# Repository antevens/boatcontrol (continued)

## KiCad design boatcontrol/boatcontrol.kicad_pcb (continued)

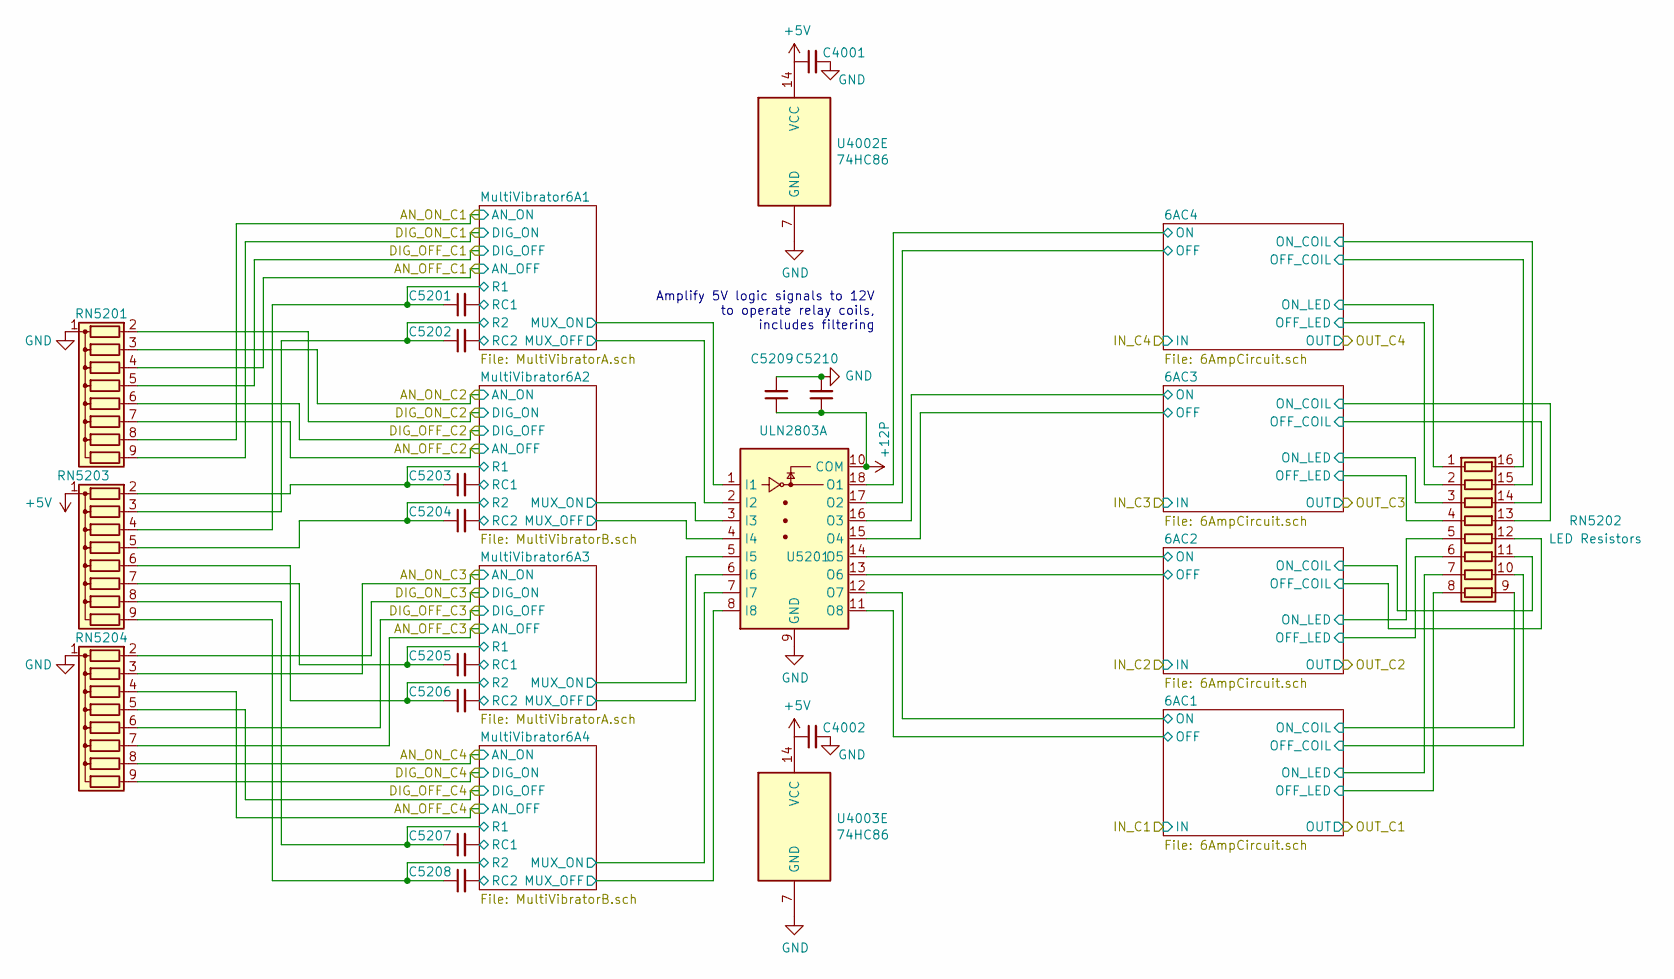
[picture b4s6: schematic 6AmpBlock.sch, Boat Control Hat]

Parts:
C4001, C4002, C7910: 0.1uF; C_Disc_D7.5mm_W5.0mm_P5.00mm
C5201, C5202, C5203, C5204, C5205, C5206, C5207, C5208: 1µF; C_Disc_D7.5mm_W5.0mm_P5.00mm
C7909: 10uF; C_Disc_D7.5mm_W5.0mm_P5.00mm
RN7901, RN7904: 100KΩ; R_Array_SIP9; Manufacturer_Part_Number 4609X-101-105LF
RN7902: 680Ω; DIP254P762X432-16P
RN7903: 10MΩ; R_Array_SIP9
U7901: ULN2803A; DIP-18_W7.62mm
U7902, U7903: 74HC86; DIP-14_W7.62mm

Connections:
230V_AC_C1_OFF: RN7901.4 (R3); also elsewhere on the board
230V_AC_C1_ON: RN7901.8 (R7); also elsewhere on the board
230V_AC_C2_OFF: RN7901.7 (R6); also elsewhere on the board
230V_AC_C2_ON: RN7901.3 (R2); also elsewhere on the board
230V_AC_C3_OFF: RN7904.7 (R6); also elsewhere on the board
230V_AC_C3_ON: RN7904.3 (R2); also elsewhere on the board
230V_AC_C4_OFF: RN7904.4 (R3); also elsewhere on the board
230V_AC_C4_ON: RN7904.8 (R7); also elsewhere on the board
+5V: C4001.1, C4002.1, RN7903.1 (common), U7902.14 (VCC), U7903.14 (VCC); also elsewhere on the board
+12P: C7909.1, C7910.1, U7901.10 (COM); also elsewhere on the board
/Mixed 12V DC / 230V AC Common Bank/12V DC 6A Block/MultiVibrator6A1/RC1: C5201.2; also elsewhere on the board
/Mixed 12V DC / 230V AC Common Bank/12V DC 6A Block/MultiVibrator6A1/RC2: C5202.2; also elsewhere on the board
/Mixed 12V DC / 230V AC Common Bank/12V DC 6A Block/MultiVibrator6A2/RC1: C5203.2; also elsewhere on the board
/Mixed 12V DC / 230V AC Common Bank/12V DC 6A Block/MultiVibrator6A2/RC2: C5204.2; also elsewhere on the board
/Mixed 12V DC / 230V AC Common Bank/12V DC 6A Block/MultiVibrator6A3/RC1: C5205.2; also elsewhere on the board
/Mixed 12V DC / 230V AC Common Bank/12V DC 6A Block/MultiVibrator6A3/RC2: C5206.2; also elsewhere on the board
/Mixed 12V DC / 230V AC Common Bank/12V DC 6A Block/MultiVibrator6A4/RC1: C5207.2; also elsewhere on the board
/Mixed 12V DC / 230V AC Common Bank/12V DC 6A Block/MultiVibrator6A4/RC2: C5208.2; also elsewhere on the board
/Mixed 12V DC / 230V AC Common Bank/230V AC 6A Block/6AC1/OFF: U7901.11 (O8); also elsewhere on the board
/Mixed 12V DC / 230V AC Common Bank/230V AC 6A Block/6AC1/OFF_COIL: RN7902.10 (R7.2); also elsewhere on the board
/Mixed 12V DC / 230V AC Common Bank/230V AC 6A Block/6AC1/OFF_LED: RN7902.8 (R8.1); also elsewhere on the board
/Mixed 12V DC / 230V AC Common Bank/230V AC 6A Block/6AC1/ON: U7901.12 (O7); also elsewhere on the board
/Mixed 12V DC / 230V AC Common Bank/230V AC 6A Block/6AC1/ON_COIL: RN7902.9 (R8.2); also elsewhere on the board
/Mixed 12V DC / 230V AC Common Bank/230V AC 6A Block/6AC1/ON_LED: RN7902.7 (R7.1); also elsewhere on the board
/Mixed 12V DC / 230V AC Common Bank/230V AC 6A Block/6AC2/OFF: U7901.13 (O6); also elsewhere on the board
/Mixed 12V DC / 230V AC Common Bank/230V AC 6A Block/6AC2/OFF_COIL: RN7902.12 (R5.2); also elsewhere on the board
/Mixed 12V DC / 230V AC Common Bank/230V AC 6A Block/6AC2/OFF_LED: RN7902.6 (R6.1); also elsewhere on the board
/Mixed 12V DC / 230V AC Common Bank/230V AC 6A Block/6AC2/ON: U7901.14 (O5); also elsewhere on the board
/Mixed 12V DC / 230V AC Common Bank/230V AC 6A Block/6AC2/ON_COIL: RN7902.11 (R6.2); also elsewhere on the board
/Mixed 12V DC / 230V AC Common Bank/230V AC 6A Block/6AC2/ON_LED: RN7902.5 (R5.1); also elsewhere on the board
/Mixed 12V DC / 230V AC Common Bank/230V AC 6A Block/6AC3/OFF: U7901.15 (O4); also elsewhere on the board
/Mixed 12V DC / 230V AC Common Bank/230V AC 6A Block/6AC3/OFF_COIL: RN7902.14 (R3.2); also elsewhere on the board
/Mixed 12V DC / 230V AC Common Bank/230V AC 6A Block/6AC3/OFF_LED: RN7902.4 (R4.1); also elsewhere on the board
/Mixed 12V DC / 230V AC Common Bank/230V AC 6A Block/6AC3/ON: U7901.16 (O3); also elsewhere on the board
/Mixed 12V DC / 230V AC Common Bank/230V AC 6A Block/6AC3/ON_COIL: RN7902.13 (R4.2); also elsewhere on the board
/Mixed 12V DC / 230V AC Common Bank/230V AC 6A Block/6AC3/ON_LED: RN7902.3 (R3.1); also elsewhere on the board
/Mixed 12V DC / 230V AC Common Bank/230V AC 6A Block/6AC4/OFF: U7901.17 (O2); also elsewhere on the board
/Mixed 12V DC / 230V AC Common Bank/230V AC 6A Block/6AC4/OFF_COIL: RN7902.16 (R1.2); also elsewhere on the board
/Mixed 12V DC / 230V AC Common Bank/230V AC 6A Block/6AC4/OFF_LED: RN7902.2 (R2.1); also elsewhere on the board
/Mixed 12V DC / 230V AC Common Bank/230V AC 6A Block/6AC4/ON: U7901.18 (O1); also elsewhere on the board
/Mixed 12V DC / 230V AC Common Bank/230V AC 6A Block/6AC4/ON_COIL: RN7902.15 (R2.2); also elsewhere on the board
/Mixed 12V DC / 230V AC Common Bank/230V AC 6A Block/6AC4/ON_LED: RN7902.1 (R1.1); also elsewhere on the board
/Mixed 12V DC / 230V AC Common Bank/230V AC 6A Block/DIG_OFF_C1: RN7901.5 (R4); also elsewhere on the board
/Mixed 12V DC / 230V AC Common Bank/230V AC 6A Block/DIG_OFF_C2: RN7901.6 (R5); also elsewhere on the board
/Mixed 12V DC / 230V AC Common Bank/230V AC 6A Block/DIG_OFF_C3: RN7904.6 (R5); also elsewhere on the board
/Mixed 12V DC / 230V AC Common Bank/230V AC 6A Block/DIG_OFF_C4: RN7904.5 (R4); also elsewhere on the board
/Mixed 12V DC / 230V AC Common Bank/230V AC 6A Block/DIG_ON_C1: RN7901.9 (R8); also elsewhere on the board
/Mixed 12V DC / 230V AC Common Bank/230V AC 6A Block/DIG_ON_C2: RN7901.2 (R1); also elsewhere on the board
/Mixed 12V DC / 230V AC Common Bank/230V AC 6A Block/DIG_ON_C3: RN7904.2 (R1); also elsewhere on the board
/Mixed 12V DC / 230V AC Common Bank/230V AC 6A Block/DIG_ON_C4: RN7904.9 (R8); also elsewhere on the board
/Mixed 12V DC / 230V AC Common Bank/230V AC 6A Block/MultiVibrator6A1/MUX_OFF: U7901.2 (I2); also elsewhere on the board
/Mixed 12V DC / 230V AC Common Bank/230V AC 6A Block/MultiVibrator6A1/MUX_ON: U7901.1 (I1); also elsewhere on the board
/Mixed 12V DC / 230V AC Common Bank/230V AC 6A Block/MultiVibrator6A2/MUX_OFF: U7901.4 (I4); also elsewhere on the board
/Mixed 12V DC / 230V AC Common Bank/230V AC 6A Block/MultiVibrator6A2/MUX_ON: U7901.3 (I3); also elsewhere on the board
/Mixed 12V DC / 230V AC Common Bank/230V AC 6A Block/MultiVibrator6A3/MUX_OFF: U7901.6 (I6); also elsewhere on the board
/Mixed 12V DC / 230V AC Common Bank/230V AC 6A Block/MultiVibrator6A3/MUX_ON: U7901.5 (I5); also elsewhere on the board
/Mixed 12V DC / 230V AC Common Bank/230V AC 6A Block/MultiVibrator6A4/MUX_OFF: U7901.8 (I8); also elsewhere on the board
/Mixed 12V DC / 230V AC Common Bank/230V AC 6A Block/MultiVibrator6A4/MUX_ON: U7901.7 (I7); also elsewhere on the board
GND: C4001.2, C4002.2, C7909.2, C7910.2, RN7901.1 (common), RN7904.1 (common), U7901.9 (GND), U7902.7 (GND), U7903.7 (GND); also elsewhere on the board

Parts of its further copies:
C5209: 10uF; C_Disc_D7.5mm_W5.0mm_P5.00mm
C5210, C6701, C6702: 0.1uF; C_Disc_D7.5mm_W5.0mm_P5.00mm
C7901, C7902, C7903, C7904, C7905, C7906, C7907, C7908: 1µF; C_Disc_D7.5mm_W5.0mm_P5.00mm
RN5201, RN5204: 100KΩ; R_Array_SIP9; Manufacturer_Part_Number 4609X-101-105LF
RN5202: 680Ω; DIP254P762X432-16P
RN5203: 10MΩ; R_Array_SIP9
U4002, U4003: 74HC86; DIP-14_W7.62mm
U5201: ULN2803A; DIP-18_W7.62mm

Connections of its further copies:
12V_DC_C17_OFF: RN5201.4 (R3), U4002.5; also elsewhere on the board
12V_DC_C17_ON: RN5201.8 (R7), U4002.2; also elsewhere on the board
12V_DC_C18_OFF: RN5201.7 (R6), U4002.13; also elsewhere on the board
12V_DC_C18_ON: RN5201.3 (R2), U4002.10; also elsewhere on the board
12V_DC_C19_OFF: RN5204.7 (R6), U4003.5; also elsewhere on the board
12V_DC_C19_ON: RN5204.3 (R2), U4003.2; also elsewhere on the board
12V_DC_C20_OFF: RN5204.4 (R3), U4003.13; also elsewhere on the board
12V_DC_C20_ON: RN5204.8 (R7), U4003.10; also elsewhere on the board
+5V: C6701.1, C6702.1, RN5203.1 (common), U4002.14 (VCC), U4003.14 (VCC); also elsewhere on the board
+12P: C5209.1, C5210.1, U5201.10 (COM); also elsewhere on the board
/Mixed 12V DC / 230V AC Common Bank/12V DC 6A Block/6AC1/OFF: U5201.11 (O8); also elsewhere on the board
/Mixed 12V DC / 230V AC Common Bank/12V DC 6A Block/6AC1/OFF_COIL: RN5202.10 (R7.2); also elsewhere on the board
/Mixed 12V DC / 230V AC Common Bank/12V DC 6A Block/6AC1/OFF_LED: RN5202.8 (R8.1); also elsewhere on the board
/Mixed 12V DC / 230V AC Common Bank/12V DC 6A Block/6AC1/ON: U5201.12 (O7); also elsewhere on the board
/Mixed 12V DC / 230V AC Common Bank/12V DC 6A Block/6AC1/ON_COIL: RN5202.9 (R8.2); also elsewhere on the board
/Mixed 12V DC / 230V AC Common Bank/12V DC 6A Block/6AC1/ON_LED: RN5202.7 (R7.1); also elsewhere on the board
/Mixed 12V DC / 230V AC Common Bank/12V DC 6A Block/6AC2/OFF: U5201.13 (O6); also elsewhere on the board
/Mixed 12V DC / 230V AC Common Bank/12V DC 6A Block/6AC2/OFF_COIL: RN5202.12 (R5.2); also elsewhere on the board
/Mixed 12V DC / 230V AC Common Bank/12V DC 6A Block/6AC2/OFF_LED: RN5202.6 (R6.1); also elsewhere on the board
/Mixed 12V DC / 230V AC Common Bank/12V DC 6A Block/6AC2/ON: U5201.14 (O5); also elsewhere on the board
/Mixed 12V DC / 230V AC Common Bank/12V DC 6A Block/6AC2/ON_COIL: RN5202.11 (R6.2); also elsewhere on the board
/Mixed 12V DC / 230V AC Common Bank/12V DC 6A Block/6AC2/ON_LED: RN5202.5 (R5.1); also elsewhere on the board
/Mixed 12V DC / 230V AC Common Bank/12V DC 6A Block/6AC3/OFF: U5201.15 (O4); also elsewhere on the board
/Mixed 12V DC / 230V AC Common Bank/12V DC 6A Block/6AC3/OFF_COIL: RN5202.14 (R3.2); also elsewhere on the board
/Mixed 12V DC / 230V AC Common Bank/12V DC 6A Block/6AC3/OFF_LED: RN5202.4 (R4.1); also elsewhere on the board
/Mixed 12V DC / 230V AC Common Bank/12V DC 6A Block/6AC3/ON: U5201.16 (O3); also elsewhere on the board
/Mixed 12V DC / 230V AC Common Bank/12V DC 6A Block/6AC3/ON_COIL: RN5202.13 (R4.2); also elsewhere on the board
/Mixed 12V DC / 230V AC Common Bank/12V DC 6A Block/6AC3/ON_LED: RN5202.3 (R3.1); also elsewhere on the board
/Mixed 12V DC / 230V AC Common Bank/12V DC 6A Block/6AC4/OFF: U5201.17 (O2); also elsewhere on the board
/Mixed 12V DC / 230V AC Common Bank/12V DC 6A Block/6AC4/OFF_COIL: RN5202.16 (R1.2); also elsewhere on the board
/Mixed 12V DC / 230V AC Common Bank/12V DC 6A Block/6AC4/OFF_LED: RN5202.2 (R2.1); also elsewhere on the board
/Mixed 12V DC / 230V AC Common Bank/12V DC 6A Block/6AC4/ON: U5201.18 (O1); also elsewhere on the board
/Mixed 12V DC / 230V AC Common Bank/12V DC 6A Block/6AC4/ON_COIL: RN5202.15 (R2.2); also elsewhere on the board
/Mixed 12V DC / 230V AC Common Bank/12V DC 6A Block/6AC4/ON_LED: RN5202.1 (R1.1); also elsewhere on the board
/Mixed 12V DC / 230V AC Common Bank/12V DC 6A Block/DIG_OFF_C1: RN5201.5 (R4), U4002.4; also elsewhere on the board
/Mixed 12V DC / 230V AC Common Bank/12V DC 6A Block/DIG_OFF_C2: RN5201.6 (R5), U4002.12; also elsewhere on the board
/Mixed 12V DC / 230V AC Common Bank/12V DC 6A Block/DIG_OFF_C3: RN5204.6 (R5), U4003.4; also elsewhere on the board
/Mixed 12V DC / 230V AC Common Bank/12V DC 6A Block/DIG_OFF_C4: RN5204.5 (R4), U4003.12; also elsewhere on the board
/Mixed 12V DC / 230V AC Common Bank/12V DC 6A Block/DIG_ON_C1: RN5201.9 (R8), U4002.1; also elsewhere on the board
/Mixed 12V DC / 230V AC Common Bank/12V DC 6A Block/DIG_ON_C2: RN5201.2 (R1), U4002.9; also elsewhere on the board
/Mixed 12V DC / 230V AC Common Bank/12V DC 6A Block/DIG_ON_C3: RN5204.2 (R1), U4003.1; also elsewhere on the board
/Mixed 12V DC / 230V AC Common Bank/12V DC 6A Block/DIG_ON_C4: RN5204.9 (R8), U4003.9; also elsewhere on the board
/Mixed 12V DC / 230V AC Common Bank/12V DC 6A Block/MultiVibrator6A1/MUX_OFF: U5201.2 (I2); also elsewhere on the board
/Mixed 12V DC / 230V AC Common Bank/12V DC 6A Block/MultiVibrator6A1/MUX_ON: U5201.1 (I1); also elsewhere on the board
/Mixed 12V DC / 230V AC Common Bank/12V DC 6A Block/MultiVibrator6A2/MUX_OFF: U5201.4 (I4); also elsewhere on the board
/Mixed 12V DC / 230V AC Common Bank/12V DC 6A Block/MultiVibrator6A2/MUX_ON: U5201.3 (I3); also elsewhere on the board
/Mixed 12V DC / 230V AC Common Bank/12V DC 6A Block/MultiVibrator6A3/MUX_OFF: U5201.6 (I6); also elsewhere on the board
/Mixed 12V DC / 230V AC Common Bank/12V DC 6A Block/MultiVibrator6A3/MUX_ON: U5201.5 (I5); also elsewhere on the board
/Mixed 12V DC / 230V AC Common Bank/12V DC 6A Block/MultiVibrator6A4/MUX_OFF: U5201.8 (I8); also elsewhere on the board
/Mixed 12V DC / 230V AC Common Bank/12V DC 6A Block/MultiVibrator6A4/MUX_ON: U5201.7 (I7); also elsewhere on the board
/Mixed 12V DC / 230V AC Common Bank/230V AC 6A Block/MultiVibrator6A1/RC1: C7901.2; also elsewhere on the board
/Mixed 12V DC / 230V AC Common Bank/230V AC 6A Block/MultiVibrator6A1/RC2: C7902.2; also elsewhere on the board
/Mixed 12V DC / 230V AC Common Bank/230V AC 6A Block/MultiVibrator6A2/RC1: C7903.2; also elsewhere on the board
/Mixed 12V DC / 230V AC Common Bank/230V AC 6A Block/MultiVibrator6A2/RC2: C7904.2; also elsewhere on the board
/Mixed 12V DC / 230V AC Common Bank/230V AC 6A Block/MultiVibrator6A3/RC1: C7905.2; also elsewhere on the board
/Mixed 12V DC / 230V AC Common Bank/230V AC 6A Block/MultiVibrator6A3/RC2: C7906.2; also elsewhere on the board
/Mixed 12V DC / 230V AC Common Bank/230V AC 6A Block/MultiVibrator6A4/RC1: C7907.2; also elsewhere on the board
/Mixed 12V DC / 230V AC Common Bank/230V AC 6A Block/MultiVibrator6A4/RC2: C7908.2; also elsewhere on the board
GND: C5209.2, C5210.2, C6701.2, C6702.2, RN5201.1 (common), RN5204.1 (common), U4002.7 (GND), U4003.7 (GND), U5201.9 (GND); also elsewhere on the board
unnamed 980: U4002.3; also elsewhere on the board
unnamed 981: U4002.6; also elsewhere on the board
unnamed 984: U4002.8; also elsewhere on the board
unnamed 985: U4002.11; also elsewhere on the board
unnamed 988: U4003.3; also elsewhere on the board
unnamed 989: U4003.6; also elsewhere on the board
unnamed 992: U4003.8; also elsewhere on the board
unnamed 993: U4003.11; also elsewhere on the board

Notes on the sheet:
Amplify 5V logic signals to 12V to operate relay coils, includes filtering

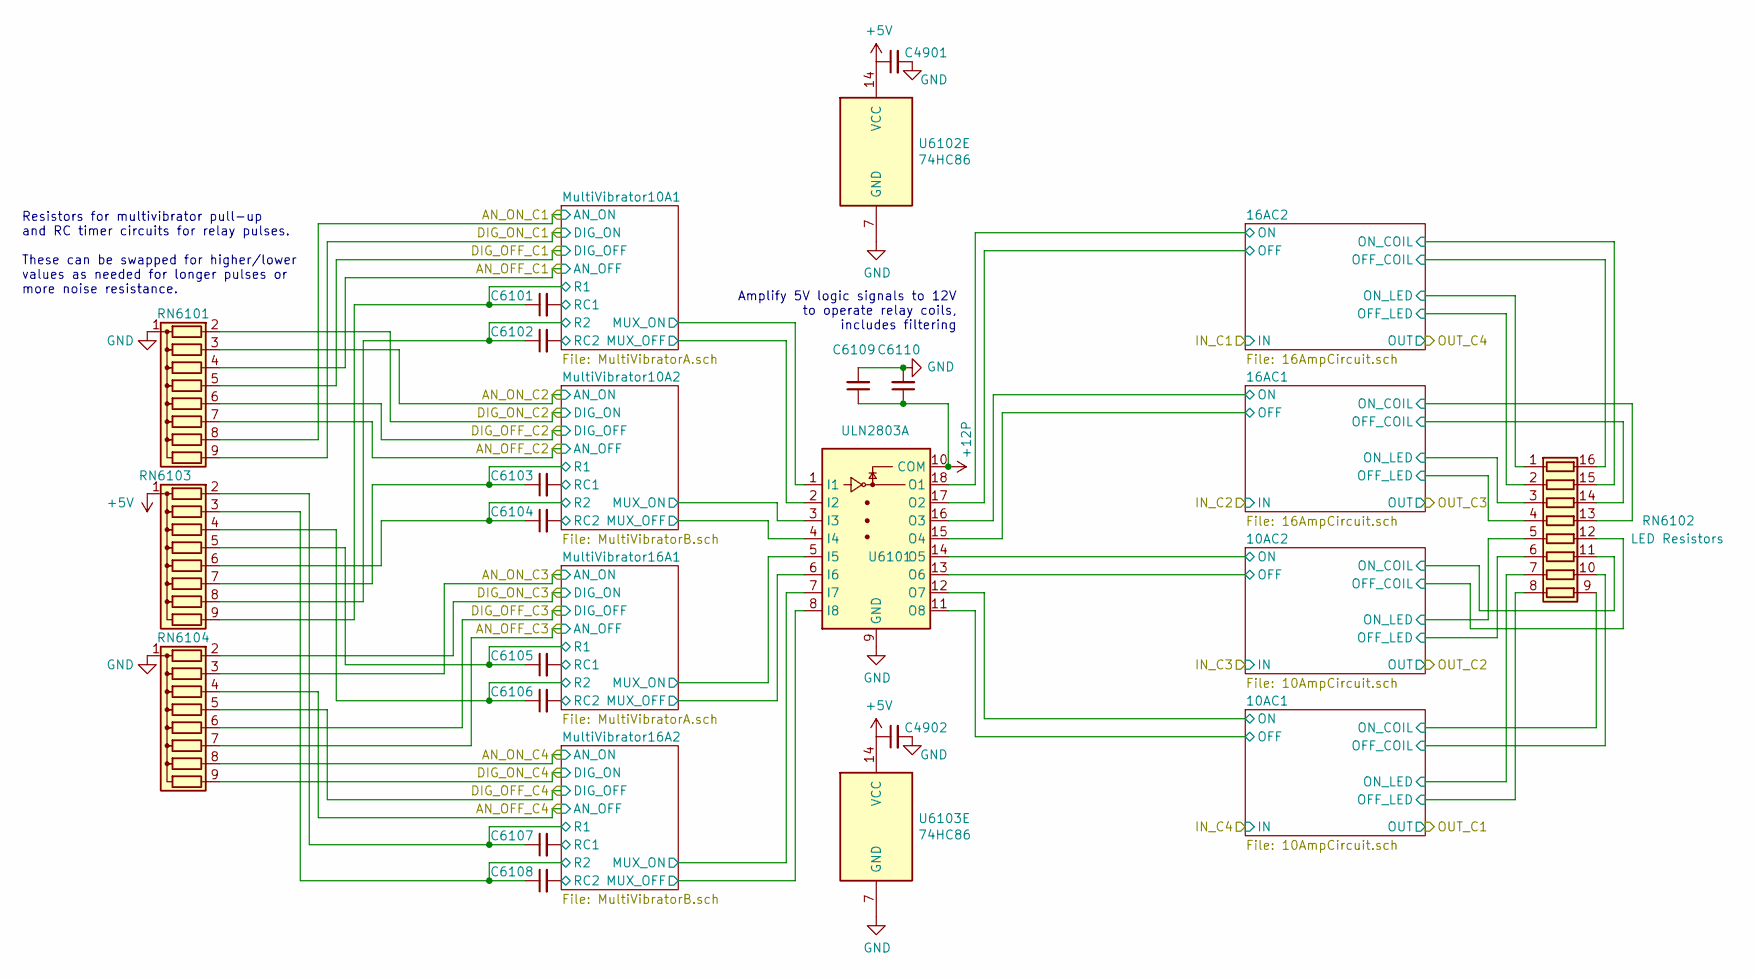
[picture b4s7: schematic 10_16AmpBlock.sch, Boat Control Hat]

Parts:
C5801, C5802, C6110: 0.1uF; C_Disc_D7.5mm_W5.0mm_P5.00mm
C6109: 10uF; C_Disc_D7.5mm_W5.0mm_P5.00mm
C7001, C7002, C7003, C7004, C7005, C7006, C7007, C7008: 1µF; C_Disc_D7.5mm_W5.0mm_P5.00mm
RN6101, RN6104: 100KΩ; R_Array_SIP9; Manufacturer_Part_Number 4609X-101-105LF
RN6102: 680Ω; DIP254P762X432-16P
RN7003: 10MΩ; R_Array_SIP9
U6101: ULN2803A; DIP-18_W7.62mm
U7002, U7003: 74HC86; DIP-14_W7.62mm

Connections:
230V_AC_C5_OFF: RN6101.4 (R3); also elsewhere on the board
230V_AC_C5_ON: RN6101.8 (R7); also elsewhere on the board
230V_AC_C6_OFF: RN6101.7 (R6); also elsewhere on the board
230V_AC_C6_ON: RN6101.3 (R2); also elsewhere on the board
230V_AC_C7_OFF: RN6104.7 (R6); also elsewhere on the board
230V_AC_C7_ON: RN6104.3 (R2); also elsewhere on the board
230V_AC_C8_OFF: RN6104.4 (R3); also elsewhere on the board
230V_AC_C8_ON: RN6104.8 (R7); also elsewhere on the board
+5V: C5801.1, C5802.1, RN7003.1 (common), U7002.14 (VCC), U7003.14 (VCC); also elsewhere on the board
+12P: C6109.1, C6110.1, U6101.10 (COM); also elsewhere on the board
/Mixed 12V DC / 230V AC Common Bank/12V DC 10/16A Block/MultiVibrator10A1/R1: C7001.1, RN7003.9 (R8); also elsewhere on the board
/Mixed 12V DC / 230V AC Common Bank/12V DC 10/16A Block/MultiVibrator10A1/R2: C7002.1, RN7003.8 (R7); also elsewhere on the board
/Mixed 12V DC / 230V AC Common Bank/12V DC 10/16A Block/MultiVibrator10A1/RC1: C7001.2; also elsewhere on the board
/Mixed 12V DC / 230V AC Common Bank/12V DC 10/16A Block/MultiVibrator10A1/RC2: C7002.2; also elsewhere on the board
/Mixed 12V DC / 230V AC Common Bank/12V DC 10/16A Block/MultiVibrator10A2/R1: C7003.1, RN7003.7 (R6); also elsewhere on the board
/Mixed 12V DC / 230V AC Common Bank/12V DC 10/16A Block/MultiVibrator10A2/R2: C7004.1, RN7003.6 (R5); also elsewhere on the board
/Mixed 12V DC / 230V AC Common Bank/12V DC 10/16A Block/MultiVibrator10A2/RC1: C7003.2; also elsewhere on the board
/Mixed 12V DC / 230V AC Common Bank/12V DC 10/16A Block/MultiVibrator10A2/RC2: C7004.2; also elsewhere on the board
/Mixed 12V DC / 230V AC Common Bank/12V DC 10/16A Block/MultiVibrator16A1/R1: C7005.1, RN7003.5 (R4); also elsewhere on the board
/Mixed 12V DC / 230V AC Common Bank/12V DC 10/16A Block/MultiVibrator16A1/R2: C7006.1, RN7003.4 (R3); also elsewhere on the board
/Mixed 12V DC / 230V AC Common Bank/12V DC 10/16A Block/MultiVibrator16A1/RC1: C7005.2; also elsewhere on the board
/Mixed 12V DC / 230V AC Common Bank/12V DC 10/16A Block/MultiVibrator16A1/RC2: C7006.2; also elsewhere on the board
/Mixed 12V DC / 230V AC Common Bank/12V DC 10/16A Block/MultiVibrator16A2/R1: C7007.1, RN7003.2 (R1); also elsewhere on the board
/Mixed 12V DC / 230V AC Common Bank/12V DC 10/16A Block/MultiVibrator16A2/R2: C7008.1, RN7003.3 (R2); also elsewhere on the board
/Mixed 12V DC / 230V AC Common Bank/12V DC 10/16A Block/MultiVibrator16A2/RC1: C7007.2; also elsewhere on the board
/Mixed 12V DC / 230V AC Common Bank/12V DC 10/16A Block/MultiVibrator16A2/RC2: C7008.2; also elsewhere on the board
/Mixed 12V DC / 230V AC Common Bank/230V AC 10/16A Block/10AC1/OFF: U6101.11 (O8); also elsewhere on the board
/Mixed 12V DC / 230V AC Common Bank/230V AC 10/16A Block/10AC1/OFF_COIL: RN6102.10 (R7.2); also elsewhere on the board
/Mixed 12V DC / 230V AC Common Bank/230V AC 10/16A Block/10AC1/OFF_LED: RN6102.8 (R8.1); also elsewhere on the board
/Mixed 12V DC / 230V AC Common Bank/230V AC 10/16A Block/10AC1/ON: U6101.12 (O7); also elsewhere on the board
/Mixed 12V DC / 230V AC Common Bank/230V AC 10/16A Block/10AC1/ON_COIL: RN6102.9 (R8.2); also elsewhere on the board
/Mixed 12V DC / 230V AC Common Bank/230V AC 10/16A Block/10AC1/ON_LED: RN6102.7 (R7.1); also elsewhere on the board
/Mixed 12V DC / 230V AC Common Bank/230V AC 10/16A Block/10AC2/OFF: U6101.13 (O6); also elsewhere on the board
/Mixed 12V DC / 230V AC Common Bank/230V AC 10/16A Block/10AC2/OFF_COIL: RN6102.12 (R5.2); also elsewhere on the board
/Mixed 12V DC / 230V AC Common Bank/230V AC 10/16A Block/10AC2/OFF_LED: RN6102.6 (R6.1); also elsewhere on the board
/Mixed 12V DC / 230V AC Common Bank/230V AC 10/16A Block/10AC2/ON: U6101.14 (O5); also elsewhere on the board
/Mixed 12V DC / 230V AC Common Bank/230V AC 10/16A Block/10AC2/ON_COIL: RN6102.11 (R6.2); also elsewhere on the board
/Mixed 12V DC / 230V AC Common Bank/230V AC 10/16A Block/10AC2/ON_LED: RN6102.5 (R5.1); also elsewhere on the board
/Mixed 12V DC / 230V AC Common Bank/230V AC 10/16A Block/16AC1/OFF: U6101.15 (O4); also elsewhere on the board
/Mixed 12V DC / 230V AC Common Bank/230V AC 10/16A Block/16AC1/OFF_COIL: RN6102.14 (R3.2); also elsewhere on the board
/Mixed 12V DC / 230V AC Common Bank/230V AC 10/16A Block/16AC1/OFF_LED: RN6102.4 (R4.1); also elsewhere on the board
/Mixed 12V DC / 230V AC Common Bank/230V AC 10/16A Block/16AC1/ON: U6101.16 (O3); also elsewhere on the board
/Mixed 12V DC / 230V AC Common Bank/230V AC 10/16A Block/16AC1/ON_COIL: RN6102.13 (R4.2); also elsewhere on the board
/Mixed 12V DC / 230V AC Common Bank/230V AC 10/16A Block/16AC1/ON_LED: RN6102.3 (R3.1); also elsewhere on the board
/Mixed 12V DC / 230V AC Common Bank/230V AC 10/16A Block/16AC2/OFF: U6101.17 (O2); also elsewhere on the board
/Mixed 12V DC / 230V AC Common Bank/230V AC 10/16A Block/16AC2/OFF_COIL: RN6102.16 (R1.2); also elsewhere on the board
/Mixed 12V DC / 230V AC Common Bank/230V AC 10/16A Block/16AC2/OFF_LED: RN6102.2 (R2.1); also elsewhere on the board
/Mixed 12V DC / 230V AC Common Bank/230V AC 10/16A Block/16AC2/ON: U6101.18 (O1); also elsewhere on the board
/Mixed 12V DC / 230V AC Common Bank/230V AC 10/16A Block/16AC2/ON_COIL: RN6102.15 (R2.2); also elsewhere on the board
/Mixed 12V DC / 230V AC Common Bank/230V AC 10/16A Block/16AC2/ON_LED: RN6102.1 (R1.1); also elsewhere on the board
/Mixed 12V DC / 230V AC Common Bank/230V AC 10/16A Block/DIG_OFF_C1: RN6101.5 (R4); also elsewhere on the board
/Mixed 12V DC / 230V AC Common Bank/230V AC 10/16A Block/DIG_OFF_C2: RN6101.6 (R5); also elsewhere on the board
/Mixed 12V DC / 230V AC Common Bank/230V AC 10/16A Block/DIG_OFF_C3: RN6104.6 (R5); also elsewhere on the board
/Mixed 12V DC / 230V AC Common Bank/230V AC 10/16A Block/DIG_OFF_C4: RN6104.5 (R4); also elsewhere on the board
/Mixed 12V DC / 230V AC Common Bank/230V AC 10/16A Block/DIG_ON_C1: RN6101.9 (R8); also elsewhere on the board
/Mixed 12V DC / 230V AC Common Bank/230V AC 10/16A Block/DIG_ON_C2: RN6101.2 (R1); also elsewhere on the board
/Mixed 12V DC / 230V AC Common Bank/230V AC 10/16A Block/DIG_ON_C3: RN6104.2 (R1); also elsewhere on the board
/Mixed 12V DC / 230V AC Common Bank/230V AC 10/16A Block/DIG_ON_C4: RN6104.9 (R8); also elsewhere on the board
/Mixed 12V DC / 230V AC Common Bank/230V AC 10/16A Block/MultiVibrator10A1/MUX_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: U6101.2 (I2); also elsewhere on the board
/Mixed 12V DC / 230V AC Common Bank/230V AC 10/16A Block/MultiVibrator10A1/MUX_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: U6101.1 (I1); also elsewhere on the board
/Mixed 12V DC / 230V AC Common Bank/230V AC 10/16A Block/MultiVibrator10A2/MUX_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: U6101.4 (I4); also elsewhere on the board
/Mixed 12V DC / 230V AC Common Bank/230V AC 10/16A Block/MultiVibrator10A2/MUX_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: U6101.3 (I3); also elsewhere on the board
/Mixed 12V DC / 230V AC Common Bank/230V AC 10/16A Block/MultiVibrator16A1/MUX_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: U6101.6 (I6); also elsewhere on the board
/Mixed 12V DC / 230V AC Common Bank/230V AC 10/16A Block/MultiVibrator16A1/MUX_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: U6101.5 (I5); also elsewhere on the board
/Mixed 12V DC / 230V AC Common Bank/230V AC 10/16A Block/MultiVibrator16A2/MUX_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: U6101.8 (I8); also elsewhere on the board
/Mixed 12V DC / 230V AC Common Bank/230V AC 10/16A Block/MultiVibrator16A2/MUX_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: U6101.7 (I7); also elsewhere on the board
GND: C5801.2, C5802.2, C6109.2, C6110.2, RN6101.1 (common), RN6104.1 (common), U6101.9 (GND), U7002.7 (GND), U7003.7 (GND); also elsewhere on the board

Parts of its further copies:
C4901, C4902, C7010: 0.1uF; C_Disc_D7.5mm_W5.0mm_P5.00mm
C6101, C6102, C6103, C6104, C6105, C6106, C6107, C6108: 1µF; C_Disc_D7.5mm_W5.0mm_P5.00mm
C7009: 10uF; C_Disc_D7.5mm_W5.0mm_P5.00mm
RN6103: 10MΩ; R_Array_SIP9
RN7001, RN7004: 100KΩ; R_Array_SIP9; Manufacturer_Part_Number 4609X-101-105LF
RN7002: 680Ω; DIP254P762X432-16P
U6102, U6103: 74HC86; DIP-14_W7.62mm
U7001: ULN2803A; DIP-18_W7.62mm

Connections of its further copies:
12V_DC_C21_OFF: RN7001.4 (R3); also elsewhere on the board
12V_DC_C21_ON: RN7001.8 (R7); also elsewhere on the board
12V_DC_C22_OFF: RN7001.7 (R6); also elsewhere on the board
12V_DC_C22_ON: RN7001.3 (R2); also elsewhere on the board
12V_DC_C23_OFF: RN7004.7 (R6); also elsewhere on the board
12V_DC_C23_ON: RN7004.3 (R2); also elsewhere on the board
12V_DC_C24_OFF: RN7004.4 (R3); also elsewhere on the board
12V_DC_C24_ON: RN7004.8 (R7); also elsewhere on the board
230V_AC_C5_OFF: U6102.5; also elsewhere on the board
230V_AC_C5_ON: U6102.2; also elsewhere on the board
230V_AC_C6_OFF: U6102.13; also elsewhere on the board
230V_AC_C6_ON: U6102.10; also elsewhere on the board
230V_AC_C7_OFF: U6103.5; also elsewhere on the board
230V_AC_C7_ON: U6103.2; also elsewhere on the board
230V_AC_C8_OFF: U6103.13; also elsewhere on the board
230V_AC_C8_ON: U6103.10; also elsewhere on the board
+5V: C4901.1, C4902.1, RN6103.1 (common), U6102.14 (VCC), U6103.14 (VCC); also elsewhere on the board
+12P: C7009.1, C7010.1, U7001.10 (COM); also elsewhere on the board
/Mixed 12V DC / 230V AC Common Bank/12V DC 10/16A Block/10AC1/OFF: U7001.11 (O8); also elsewhere on the board
/Mixed 12V DC / 230V AC Common Bank/12V DC 10/16A Block/10AC1/OFF_COIL: RN7002.10 (R7.2); also elsewhere on the board
/Mixed 12V DC / 230V AC Common Bank/12V DC 10/16A Block/10AC1/OFF_LED: RN7002.8 (R8.1); also elsewhere on the board
/Mixed 12V DC / 230V AC Common Bank/12V DC 10/16A Block/10AC1/ON: U7001.12 (O7); also elsewhere on the board
/Mixed 12V DC / 230V AC Common Bank/12V DC 10/16A Block/10AC1/ON_COIL: RN7002.9 (R8.2); also elsewhere on the board
/Mixed 12V DC / 230V AC Common Bank/12V DC 10/16A Block/10AC1/ON_LED: RN7002.7 (R7.1); also elsewhere on the board
/Mixed 12V DC / 230V AC Common Bank/12V DC 10/16A Block/10AC2/OFF: U7001.13 (O6); also elsewhere on the board
/Mixed 12V DC / 230V AC Common Bank/12V DC 10/16A Block/10AC2/OFF_COIL: RN7002.12 (R5.2); also elsewhere on the board
/Mixed 12V DC / 230V AC Common Bank/12V DC 10/16A Block/10AC2/OFF_LED: RN7002.6 (R6.1); also elsewhere on the board
/Mixed 12V DC / 230V AC Common Bank/12V DC 10/16A Block/10AC2/ON: U7001.14 (O5); also elsewhere on the board
/Mixed 12V DC / 230V AC Common Bank/12V DC 10/16A Block/10AC2/ON_COIL: RN7002.11 (R6.2); also elsewhere on the board
/Mixed 12V DC / 230V AC Common Bank/12V DC 10/16A Block/10AC2/ON_LED: RN7002.5 (R5.1); also elsewhere on the board
/Mixed 12V DC / 230V AC Common Bank/12V DC 10/16A Block/16AC1/OFF: U7001.15 (O4); also elsewhere on the board
/Mixed 12V DC / 230V AC Common Bank/12V DC 10/16A Block/16AC1/OFF_COIL: RN7002.14 (R3.2); also elsewhere on the board
/Mixed 12V DC / 230V AC Common Bank/12V DC 10/16A Block/16AC1/OFF_LED: RN7002.4 (R4.1); also elsewhere on the board
/Mixed 12V DC / 230V AC Common Bank/12V DC 10/16A Block/16AC1/ON: U7001.16 (O3); also elsewhere on the board
/Mixed 12V DC / 230V AC Common Bank/12V DC 10/16A Block/16AC1/ON_COIL: RN7002.13 (R4.2); also elsewhere on the board
/Mixed 12V DC / 230V AC Common Bank/12V DC 10/16A Block/16AC1/ON_LED: RN7002.3 (R3.1); also elsewhere on the board
/Mixed 12V DC / 230V AC Common Bank/12V DC 10/16A Block/16AC2/OFF: U7001.17 (O2); also elsewhere on the board
/Mixed 12V DC / 230V AC Common Bank/12V DC 10/16A Block/16AC2/OFF_COIL: RN7002.16 (R1.2); also elsewhere on the board
/Mixed 12V DC / 230V AC Common Bank/12V DC 10/16A Block/16AC2/OFF_LED: RN7002.2 (R2.1); also elsewhere on the board
/Mixed 12V DC / 230V AC Common Bank/12V DC 10/16A Block/16AC2/ON: U7001.18 (O1); also elsewhere on the board
/Mixed 12V DC / 230V AC Common Bank/12V DC 10/16A Block/16AC2/ON_COIL: RN7002.15 (R2.2); also elsewhere on the board
/Mixed 12V DC / 230V AC Common Bank/12V DC 10/16A Block/16AC2/ON_LED: RN7002.1 (R1.1); also elsewhere on the board
/Mixed 12V DC / 230V AC Common Bank/12V DC 10/16A Block/DIG_OFF_C1: RN7001.5 (R4); also elsewhere on the board
/Mixed 12V DC / 230V AC Common Bank/12V DC 10/16A Block/DIG_OFF_C2: RN7001.6 (R5); also elsewhere on the board
/Mixed 12V DC / 230V AC Common Bank/12V DC 10/16A Block/DIG_OFF_C3: RN7004.6 (R5); also elsewhere on the board
/Mixed 12V DC / 230V AC Common Bank/12V DC 10/16A Block/DIG_OFF_C4: RN7004.5 (R4); also elsewhere on the board
/Mixed 12V DC / 230V AC Common Bank/12V DC 10/16A Block/DIG_ON_C1: RN7001.9 (R8); also elsewhere on the board
/Mixed 12V DC / 230V AC Common Bank/12V DC 10/16A Block/DIG_ON_C2: RN7001.2 (R1); also elsewhere on the board
/Mixed 12V DC / 230V AC Common Bank/12V DC 10/16A Block/DIG_ON_C3: RN7004.2 (R1); also elsewhere on the board
/Mixed 12V DC / 230V AC Common Bank/12V DC 10/16A Block/DIG_ON_C4: RN7004.9 (R8); also elsewhere on the board
/Mixed 12V DC / 230V AC Common Bank/12V DC 10/16A Block/MultiVibrator10A1/MUX_O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: U7001.2 (I2); also elsewhere on the board
/Mixed 12V DC / 230V AC Common Bank/12V DC 10/16A Block/MultiVibrator10A1/MUX_ON: U7001.1 (I1); also elsewhere on the board
/Mixed 12V DC / 230V AC Common Bank/12V DC 10/16A Block/MultiVibrator10A2/MUX_O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: U7001.4 (I4); also elsewhere on the board
/Mixed 12V DC / 230V AC Common Bank/12V DC 10/16A Block/MultiVibrator10A2/MUX_ON: U7001.3 (I3); also elsewhere on the board
/Mixed 12V DC / 230V AC Common Bank/12V DC 10/16A Block/MultiVibrator16A1/MUX_O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: U7001.6 (I6); also elsewhere on the board
/Mixed 12V DC / 230V AC Common Bank/12V DC 10/16A Block/MultiVibrator16A1/MUX_ON: U7001.5 (I5); also elsewhere on the board
/Mixed 12V DC / 230V AC Common Bank/12V DC 10/16A Block/MultiVibrator16A2/MUX_O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: U7001.8 (I8); also elsewhere on the board
/Mixed 12V DC / 230V AC Common Bank/12V DC 10/16A Block/MultiVibrator16A2/MUX_ON: U7001.7 (I7); also elsewhere on the board
/Mixed 12V DC / 230V AC Common Bank/230V AC 10/16A Block/DIG_OFF_C1: U6102.4; also elsewhere on the board
/Mixed 12V DC / 230V AC Common Bank/230V AC 10/16A Block/DIG_OFF_C2: U6102.12; also elsewhere on the board
/Mixed 12V DC / 230V AC Common Bank/230V AC 10/16A Block/DIG_OFF_C3: U6103.4; also elsewhere on the board
/Mixed 12V DC / 230V AC Common Bank/230V AC 10/16A Block/DIG_OFF_C4: U6103.12; also elsewhere on the board
/Mixed 12V DC / 230V AC Common Bank/230V AC 10/16A Block/DIG_ON_C1: U6102.1; also elsewhere on the board
/Mixed 12V DC / 230V AC Common Bank/230V AC 10/16A Block/DIG_ON_C2: U6102.9; also elsewhere on the board
/Mixed 12V DC / 230V AC Common Bank/230V AC 10/16A Block/DIG_ON_C3: U6103.1; also elsewhere on the board
/Mixed 12V DC / 230V AC Common Bank/230V AC 10/16A Block/DIG_ON_C4: U6103.9; also elsewhere on the board
/Mixed 12V DC / 230V AC Common Bank/230V AC 10/16A Block/MultiVibrator10A1/R1: C6101.1, RN6103.9 (R8); also elsewhere on the board
/Mixed 12V DC / 230V AC Common Bank/230V AC 10/16A Block/MultiVibrator10A1/R2: C6102.1, RN6103.8 (R7); also elsewhere on the board
/Mixed 12V DC / 230V AC Common Bank/230V AC 10/16A Block/MultiVibrator10A1/RC1: C6101.2; also elsewhere on the board
/Mixed 12V DC / 230V AC Common Bank/230V AC 10/16A Block/MultiVibrator10A1/RC2: C6102.2; also elsewhere on the board
/Mixed 12V DC / 230V AC Common Bank/230V AC 10/16A Block/MultiVibrator10A2/R1: C6103.1, RN6103.7 (R6); also elsewhere on the board
/Mixed 12V DC / 230V AC Common Bank/230V AC 10/16A Block/MultiVibrator10A2/R2: C6104.1, RN6103.6 (R5); also elsewhere on the board
/Mixed 12V DC / 230V AC Common Bank/230V AC 10/16A Block/MultiVibrator10A2/RC1: C6103.2; also elsewhere on the board
/Mixed 12V DC / 230V AC Common Bank/230V AC 10/16A Block/MultiVibrator10A2/RC2: C6104.2; also elsewhere on the board
/Mixed 12V DC / 230V AC Common Bank/230V AC 10/16A Block/MultiVibrator16A1/R1: C6105.1, RN6103.5 (R4); also elsewhere on the board
/Mixed 12V DC / 230V AC Common Bank/230V AC 10/16A Block/MultiVibrator16A1/R2: C6106.1, RN6103.4 (R3); also elsewhere on the board
/Mixed 12V DC / 230V AC Common Bank/230V AC 10/16A Block/MultiVibrator16A1/RC1: C6105.2; also elsewhere on the board
/Mixed 12V DC / 230V AC Common Bank/230V AC 10/16A Block/MultiVibrator16A1/RC2: C6106.2; also elsewhere on the board
/Mixed 12V DC / 230V AC Common Bank/230V AC 10/16A Block/MultiVibrator16A2/R1: C6107.1, RN6103.2 (R1); also elsewhere on the board
/Mixed 12V DC / 230V AC Common Bank/230V AC 10/16A Block/MultiVibrator16A2/R2: C6108.1, RN6103.3 (R2); also elsewhere on the board
/Mixed 12V DC / 230V AC Common Bank/230V AC 10/16A Block/MultiVibrator16A2/RC1: C6107.2; also elsewhere on the board
/Mixed 12V DC / 230V AC Common Bank/230V AC 10/16A Block/MultiVibrator16A2/RC2: C6108.2; also elsewhere on the board
GND: C4901.2, C4902.2, C7009.2, C7010.2, RN7001.1 (common), RN7004.1 (common), U6102.7 (GND), U6103.7 (GND), U7001.9 (GND); also elsewhere on the board
unnamed 996: U6102.3; also elsewhere on the board
unnamed 997: U6102.6; also elsewhere on the board
unnamed 1000: U6102.8; also elsewhere on the board
unnamed 1001: U6102.11; also elsewhere on the board
unnamed 1004: U6103.3; also elsewhere on the board
unnamed 1005: U6103.6; also elsewhere on the board
unnamed 1008: U6103.8; also elsewhere on the board
unnamed 1009: U6103.11; also elsewhere on the board

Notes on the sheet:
Amplify 5V logic signals to 12V to operate relay coils, includes filtering
Resistors for multivibrator pull-up and RC timer circuits for relay pulses. These can be swapped for higher/lower values as needed for longer pulses or more noise resistance.
